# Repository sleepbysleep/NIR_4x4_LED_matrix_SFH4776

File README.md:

# NIR_4x4_LED_matrix_SFH4776
4x4 LED matrix of SFH4776 and GW CSSRM2.CM ranging in Vis/Nir

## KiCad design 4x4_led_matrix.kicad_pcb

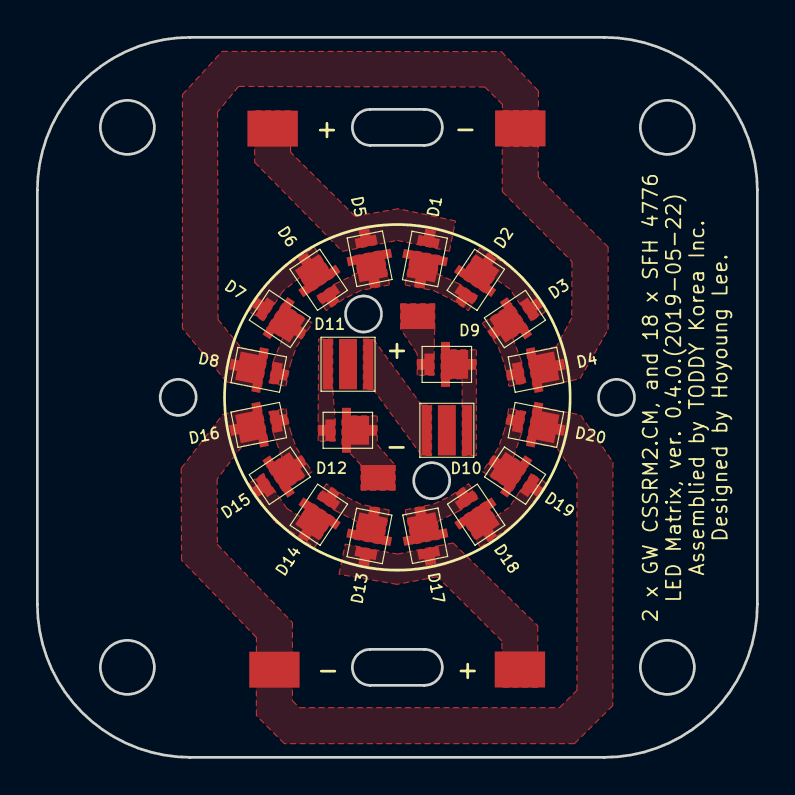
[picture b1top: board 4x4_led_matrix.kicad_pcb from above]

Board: 2 copper layers, 40.0 x 40.0 mm, 26 parts (0 on the bottom side), 21 nets, no tracks yet.

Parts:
+: ANODE_2; SMD_CUSTOM_2
+#2: ANODE_1; SMD_1P_2.8x2.0
+#3: ANODE_3; SMD_1P_2.8x2.0
-: CATHOD_1; SMD_1P_2.8x2.0
-#2: CATHOD_3; SMD_1P_2.8x2.0
-#3: CATHOD_2; SMD_CUSTOM_2
D1, D2, D3, D4, D5, D6, D7, D8, D9, D12, D13, D14, D15, D16, D17, D18, D19, D20: LED; LED-SFH4776_OSRAM_fit
D10, D11: LED; LED-GWCSSRM2.CM_OSRAM

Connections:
unnamed: D1.1, D2.2
unnamed: +#2.1, D1.2, D5.2
unnamed: D2.1, D3.2
unnamed: D3.1, D4.2
unnamed: -.1, D4.1, D8.1
unnamed: D5.1, D6.2
unnamed: D6.1, D7.2
unnamed: D7.1, D8.2
unnamed: +.1, D9.2
unnamed: D10.1, D11.2
unnamed: D9.1, D10.2
unnamed: D11.1, D12.2
unnamed: -#3.1, D12.1
unnamed: D13.1, D14.2
unnamed: +#3.1, D13.2, D17.2
unnamed: D14.1, D15.2
unnamed: D15.1, D16.2
unnamed: -#2.1, D16.1, D20.1
unnamed: D17.1, D18.2
unnamed: D18.1, D19.2
unnamed: D19.1, D20.2
